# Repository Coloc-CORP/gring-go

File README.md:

# 💍 Smart BLE Ring Project

---

## 🧠 Team

- 🛠️ **Hardware Engineers**: Mathys Pellen, Pierrick Simon
- 👨‍💻 **Software Engineers**: David Cartier, Marius Chritin

---

## 📜 Project Description

Development of an **ultra-compact smart ring** integrating:
- **Bluetooth Low Energy (BLE) communication**
- **Heart rate (BPM) measurement**
- **Activity and movement tracking**
- **Sleep monitoring**
- **Skin temperature measurement**

Mobile application dedicated to:
- Real-time collection of biometric data
- Visualization and analysis of health information
- Synchronization with **Samsung Health** using **Health Connect API**

---

## 🛠️ Project Architecture

### Hardware
- **Microcontroller**: nRF5340 (Nordic Semiconductor)
- **Main Sensors**:
  - MAX86150: Heart Rate and SpO2
  - BHI260AP: 6-axis IMU (motion detection)
  - MAX30205 (or equivalent): Skin temperature sensor
- **Charging**: Wireless charging with Qi standard (STWLC38 IC)
- **PCB**: Flexible PCB (FPC) for compact integration into a ring
- **Casing**: Titanium ring, machined or 3D printed

### Software
- **Embedded firmware**:
  - Developed with **nRF Connect SDK** (Zephyr RTOS)
  - Standard BLE GATT communication
  - OTA DFU (Firmware update over Bluetooth) supported
- **Android Application**:
  - Developed with **Android Studio**
  - BLE Central communication
  - Integration with **Samsung Health** via **Health Connect**

---

## 📂 Project Folder Structure

```plaintext
/README.md           → Main project documentation
/HW/                 → Hardware designs (schematics, PCB layouts, datasheets)
                     → 3D models of the ring (STEP, STL, F3D formats)
/SW/                 → Embedded firmware for nRF5340 (Zephyr)
                     → Android Studio mobile app project
/doc/                → Specifications, technical documents, research notes
```

---

## 🧩 Technologies and Tools

- **nRF Connect SDK** (Zephyr RTOS, Nordic Semiconductor)
- **Segger Embedded Studio** or **VS Code + nRF Connect Extensions**
- **KiCad** for PCB design
- **OnShape / SolidWorks** for 3D modeling
- **Android Studio** for mobile app development
- **GitHub** for project management and version control

---

## 📈 Roadmap

- [x] Requirements and specifications definition
- [x] Component selection
- [ ] BLE basic firmware development
- [ ] BLE mobile application creation
- [ ] First prototype PCB design
- [ ] Hardware prototype fabrication
- [ ] Full system integration and testing
- [ ] Low-power optimization
- [ ] Final miniaturization and industrialization

---

## ⚡ Inspirations

- Samsung Galaxy Ring
- Oura Ring Gen 3

---

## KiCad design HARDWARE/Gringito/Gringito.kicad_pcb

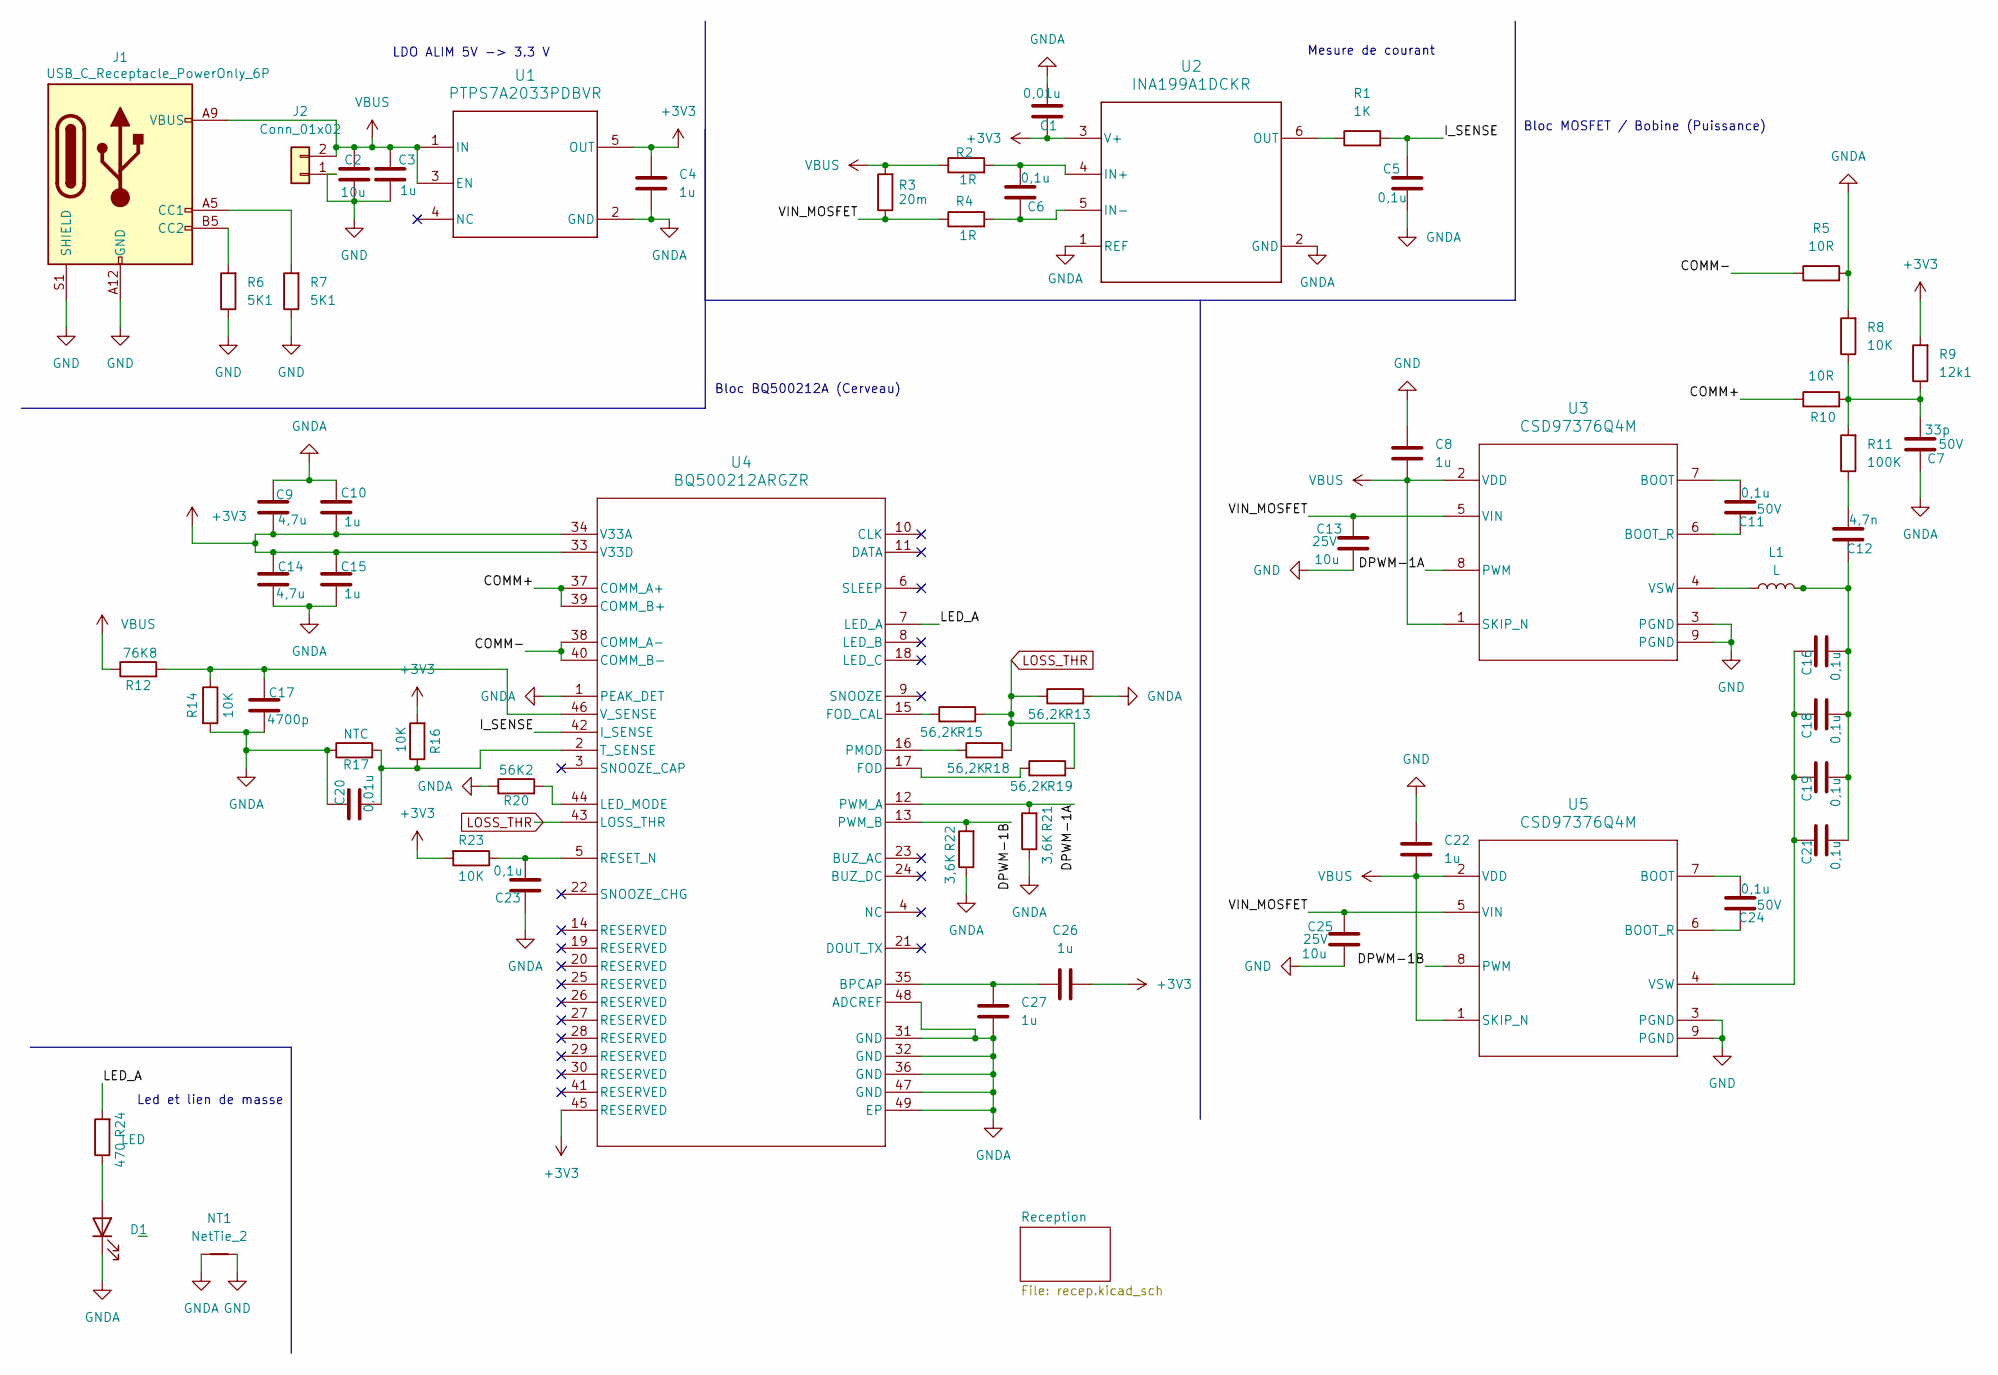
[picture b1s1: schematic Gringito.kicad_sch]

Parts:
C1, C20: 0,01u; C_0805_2012Metric
C2: 10u; C_0805_2012Metric
C3, C4, C8, C10, C15, C22, C26, C27: 1u; C_0805_2012Metric
C5, C6, C23: 0,1u; C_0805_2012Metric
C7: 33p; C_0805_2012Metric; voltage 50V
C9, C14: 4,7u; C_0805_2012Metric
C11, C24: 0,1u; C_0805_2012Metric; voltage 50V
C12: 4,7n; C_0805_2012Metric
C13: 10u; C_0805_2012Metric; Voltage 25V
C16, C18, C19, C21: 0,1u; C_1206_3216Metric_Pad1.33x1.80mm_HandSolder
C17: 4700p; C_0805_2012Metric
C25: 10u; C_0805_2012Metric; voltage 25V
D1: LED; LED_0805_2012Metric
J1: USB_C_Receptacle_PowerOnly_6P; USB_C_Receptacle_GCT_USB4135-GF-A_6P_TopMnt_Horizontal
J2: Conn_01x02; PinHeader_1x02_P2.54mm_Vertical
L1: L; SolderWire-1.5sqmm_1x02_P6mm_D1.7mm_OD3mm
NT1: NetTie_2; NetTie-2_SMD_Pad0.5mm
R1: 1K; R_0805_2012Metric_Pad1.20x1.40mm_HandSolder
R2, R4: 1R; R_0805_2012Metric_Pad1.20x1.40mm_HandSolder
R3: 20m; R_0805_2012Metric_Pad1.20x1.40mm_HandSolder
R5, R10: 10R; R_0805_2012Metric_Pad1.20x1.40mm_HandSolder
R6, R7: 5K1; R_0805_2012Metric_Pad1.20x1.40mm_HandSolder
R8, R14, R16, R23: 10K; R_0805_2012Metric_Pad1.20x1.40mm_HandSolder
R9: 12k1; R_0805_2012Metric_Pad1.20x1.40mm_HandSolder
R11: 100K; R_0805_2012Metric_Pad1.20x1.40mm_HandSolder
R12: 76K8; R_0805_2012Metric_Pad1.20x1.40mm_HandSolder
R13, R15, R18, R19: 56,2K; R_0805_2012Metric_Pad1.20x1.40mm_HandSolder
R17: NTC; R_0805_2012Metric_Pad1.20x1.40mm_HandSolder
R20: 56K2; R_0805_2012Metric_Pad1.20x1.40mm_HandSolder
R21, R22: 3,6K; R_0805_2012Metric_Pad1.20x1.40mm_HandSolder
R24: 470; R_0805_2012Metric_Pad1.20x1.40mm_HandSolder
U1: PTPS7A2033PDBVR; DBV0005A-IPC_A
U2: INA199A1DCKR; DCK0006A_N
U3, U5: CSD97376Q4M; DPC0008A
U4: BQ500212ARGZR; RGZ0048A

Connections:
+3V3: C1.1, C4.1, C9.2, C10.2, C14.1, C15.1, C26.1, R9.2, R16.2, R23.2, U1.5 (OUT), U2.3 (V+), U4.33 (V33D), U4.34 (V33A), U4.45 (RESERVED)
/COMM+: R10.1, U4.37 (COMM_A+), U4.39 (COMM_B+)
/COMM-: R5.1, U4.38 (COMM_A-), U4.40 (COMM_B-)
/DPWM-1A: R21.2, U3.8 (PWM), U4.12 (PWM_A)
/DPWM-1B: R22.2, U4.13 (PWM_B), U5.8 (PWM)
/I_SENSE: C5.1, R1.2, U4.42 (I_SENSE)
/LED_A: R24.2, U4.7 (LED_A)
/VIN_MOSFET: C13.1, C25.1, R3.1, R4.1, U3.5 (VIN), U5.5 (VIN)
GND: C2.2, C3.2, C8.2, C13.2, C22.2, C25.2, J1.A12 (GND), J1.B12 (GND), J1.S1 (SHIELD), J2.1, NT1.2, R6.1, R7.1, U3.3 (PGND), U3.9 (PGND), U3.V, U5.3 (PGND), U5.9 (PGND), U5.V
GNDA: C1.2, C4.2, C5.2, C7.1, C9.1, C10.1, C14.2, C15.2, C17.2, C20.1, C23.1, C27.1, D1.1 (K), NT1.1, R5.2, R8.2, R13.2, R14.2, R17.1, R20.1, R21.1, R22.1, U1.2 (GND), U2.1 (REF), U2.2 (GND), U4.1 (PEAK_DET), U4.31 (GND), U4.32 (GND), U4.36 (GND), U4.47 (GND), U4.48 (ADCREF), U4.49 (EP), U4.V
LOSS_THR: R13.1, R15.2, R18.2, R19.2, U4.43 (LOSS_THR)
unnamed: C7.2, R8.1, R9.1, R10.2, R11.2
unnamed: C12.1, C16.2, C18.2, C19.2, C21.2, L1.2
unnamed: C12.2, R11.1
unnamed: D1.2 (A), R24.1
unnamed: J1.A5 (CC1), R7.2
unnamed: J1.B5 (CC2), R6.2
unnamed: C6.2, R2.2, U2.4 (IN+)
unnamed: C6.1, R4.2, U2.5 (IN-)
unnamed: R1.1, U2.6 (OUT)
unnamed: C11.2, U3.7 (BOOT)
unnamed: C11.1, U3.6 (BOOT_R)
unnamed: L1.1, U3.4 (VSW)
unnamed: C26.2, C27.2, U4.35 (BPCAP)
unnamed: R19.1, U4.17 (FOD)
unnamed: R15.1, U4.15 (FOD_CAL)
unnamed: R20.2, U4.44 (LED_MODE)
unnamed: R18.1, U4.16 (PMOD)
unnamed: C23.2, R23.1, U4.5 (RESET_N)
unnamed: C20.2, R16.1, R17.2, U4.2 (T_SENSE)
unnamed: C17.1, R12.2, R14.1, U4.46 (V_SENSE)
unnamed: C24.2, U5.7 (BOOT)
unnamed: C24.1, U5.6 (BOOT_R)
unnamed: C16.1, C18.1, C19.1, C21.1, U5.4 (VSW)
VBUS: C2.1, C3.1, C8.1, C22.1, J1.A9 (VBUS), J1.B9 (VBUS), J2.2, R2.1, R3.2, R12.1, U1.1 (IN), U1.3 (EN), U3.1 (SKIP_N), U3.2 (VDD), U5.1 (SKIP_N), U5.2 (VDD)

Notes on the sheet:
Bloc BQ500212A (Cerveau)
Led et lien de masse
Bloc MOSFET / Bobine (Puissance)
LDO ALIM 5V -> 3.3 V
Mesure de courant

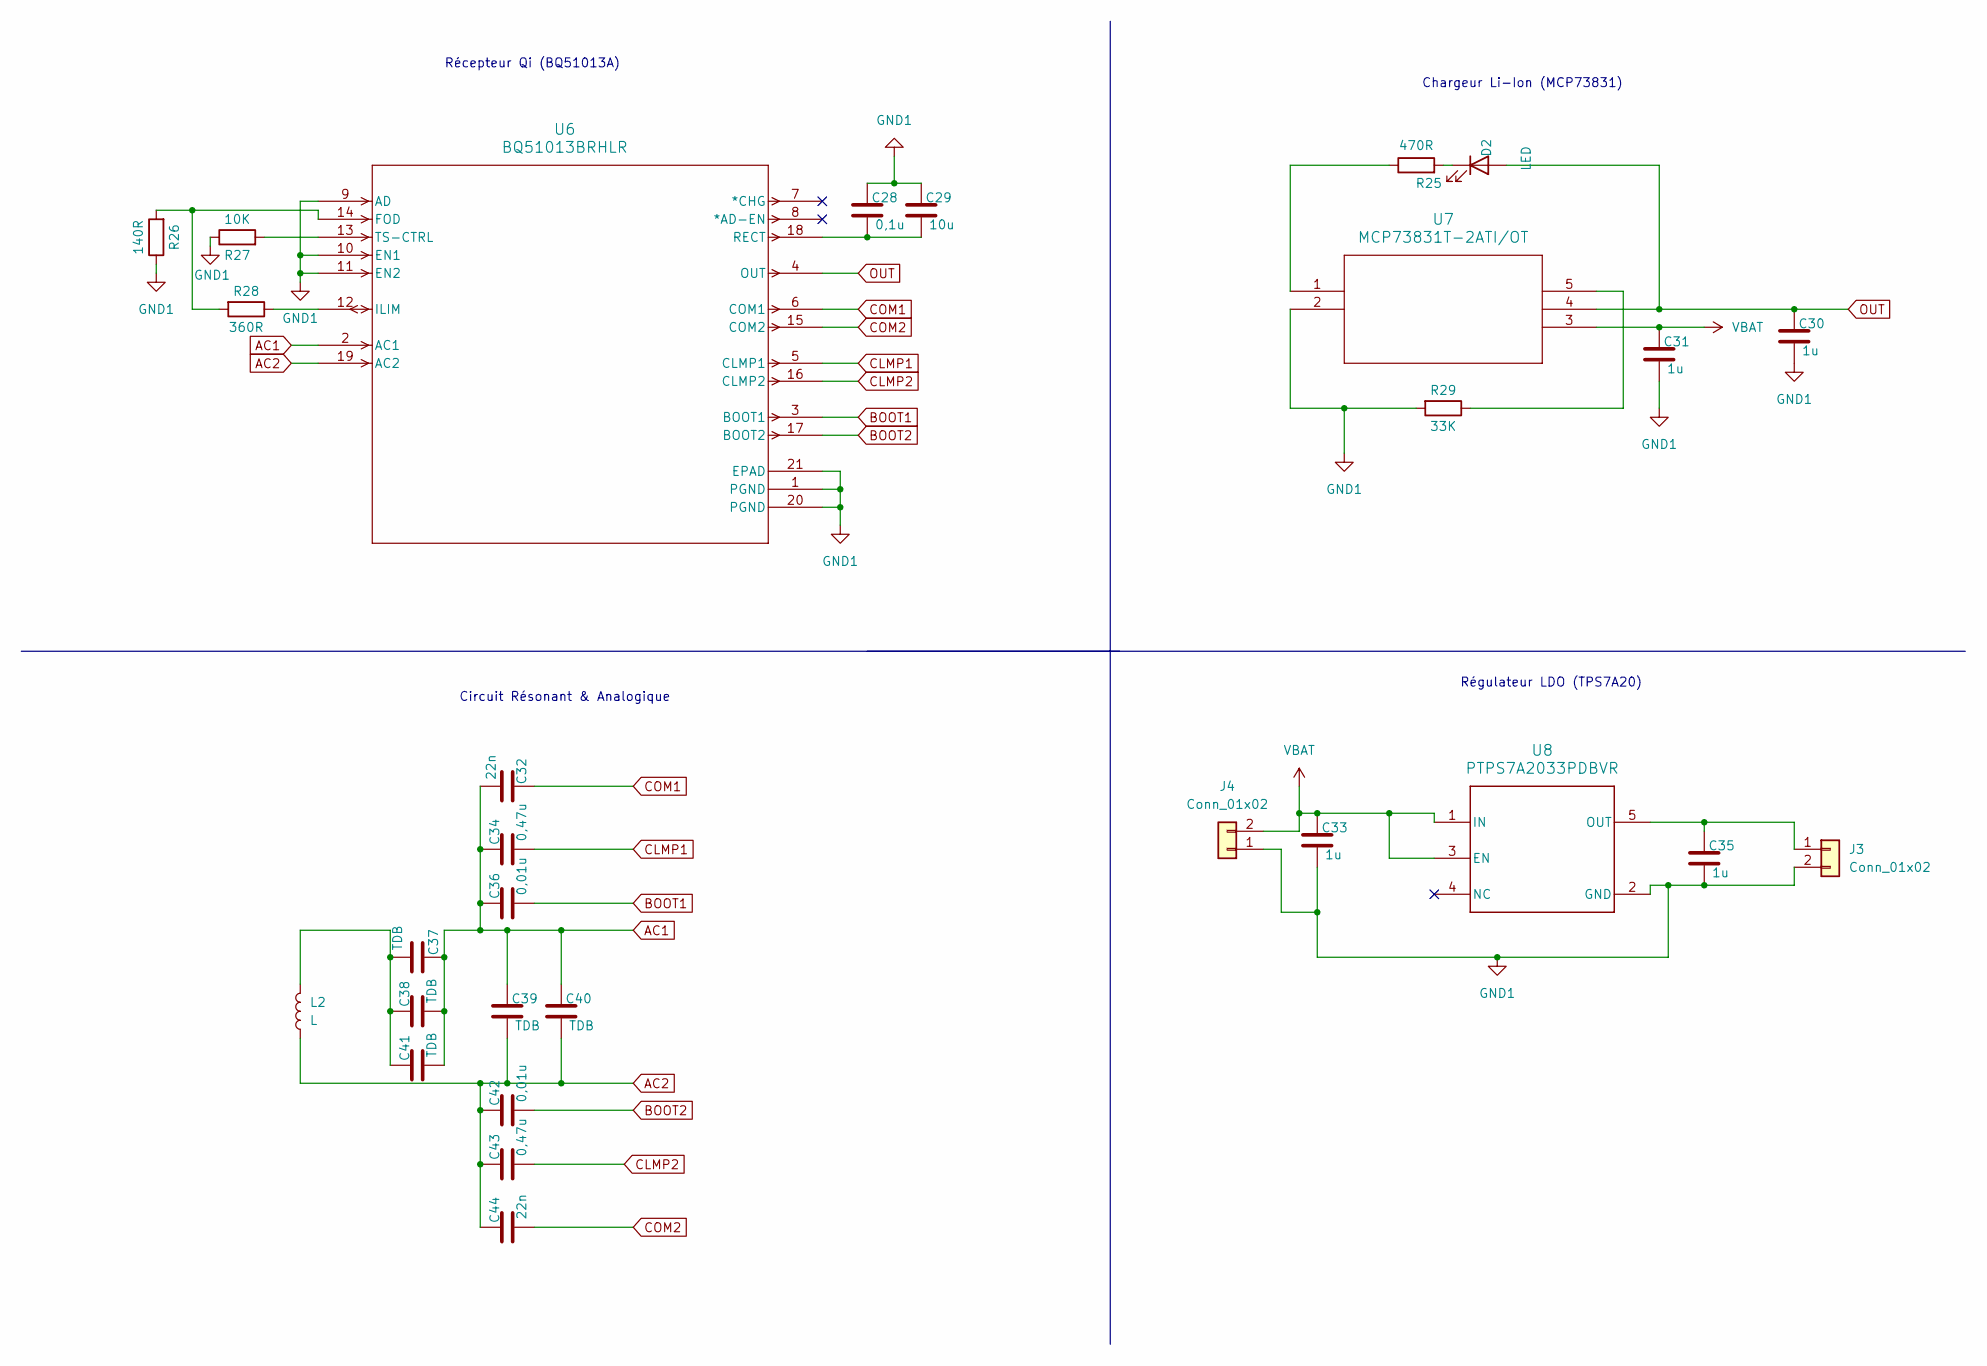
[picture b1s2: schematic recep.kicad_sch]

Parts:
C28: 0,1u; C_0805_2012Metric
C29: 10u; C_0805_2012Metric
C30, C31, C33, C35: 1u; C_0805_2012Metric
C32, C44: 22n; C_0805_2012Metric
C34, C43: 0,47u; C_0805_2012Metric
C36, C42: 0,01u; C_0805_2012Metric
C37, C38, C39, C40, C41: TDB; C_0805_2012Metric
D2: LED; LED_0805_2012Metric
J3, J4: Conn_01x02; PinHeader_1x02_P2.54mm_Vertical
L2: L; SolderWire-1.5sqmm_1x02_P6mm_D1.7mm_OD3mm
R25: 470R; R_0805_2012Metric_Pad1.20x1.40mm_HandSolder
R26: 140R; R_0805_2012Metric_Pad1.20x1.40mm_HandSolder
R27: 10K; R_0805_2012Metric_Pad1.20x1.40mm_HandSolder
R28: 360R; R_0805_2012Metric_Pad1.20x1.40mm_HandSolder
R29: 33K; R_0805_2012Metric_Pad1.20x1.40mm_HandSolder
U6: BQ51013BRHLR; RHL20_2P05X3P05
U7: MCP73831T-2ATI/OT; SOT-23-5_MC_MCH
U8: PTPS7A2033PDBVR; DBV0005A-IPC_A

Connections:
AC1: C32.2, C34.1, C36.1, C37.1, C38.2, C39.1, C40.1, C41.2, U6.2 (AC1)
AC2: C39.2, C40.2, C42.1, C43.1, C44.1, L2.1, U6.19 (AC2)
BOOT1: C36.2, U6.3 (BOOT1)
BOOT2: C42.2, U6.17 (BOOT2)
CLMP1: C34.2, U6.5 (CLMP1)
CLMP2: C43.2, U6.16 (CLMP2)
COM1: C32.1, U6.6 (COM1)
COM2: C44.2, U6.15 (COM2)
GND1: C28.1, C29.1, C30.2, C31.2, C33.2, C35.2, J3.2, J4.1, R26.1, R27.1, R29.2, U6.1 (PGND), U6.9 (AD), U6.10 (EN1), U6.11 (EN2), U6.20 (PGND), U6.21 (EPAD), U6.V, U7.2, U8.2 (GND)
unnamed: C37.2, C38.1, C41.1, L2.2
unnamed: D2.1 (K), R25.2
unnamed: C35.1, J3.1, U8.5 (OUT)
unnamed: R25.1, U7.1
unnamed: R29.1, U7.5
unnamed: R26.2, R28.2, U6.14 (FOD)
unnamed: R28.1, U6.12 (ILIM)
unnamed: C28.2, C29.2, U6.18 (RECT)
unnamed: R27.2, U6.13 (TS-CTRL)
OUT: C30.1, D2.2 (A), U6.4 (OUT), U7.4
VBAT: C31.1, C33.1, J4.2, U7.3, U8.1 (IN), U8.3 (EN)

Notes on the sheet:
Récepteur Qi (BQ51013A)
Chargeur Li-Ion (MCP73831)
Circuit Résonant & Analogique
Régulateur LDO (TPS7A20)

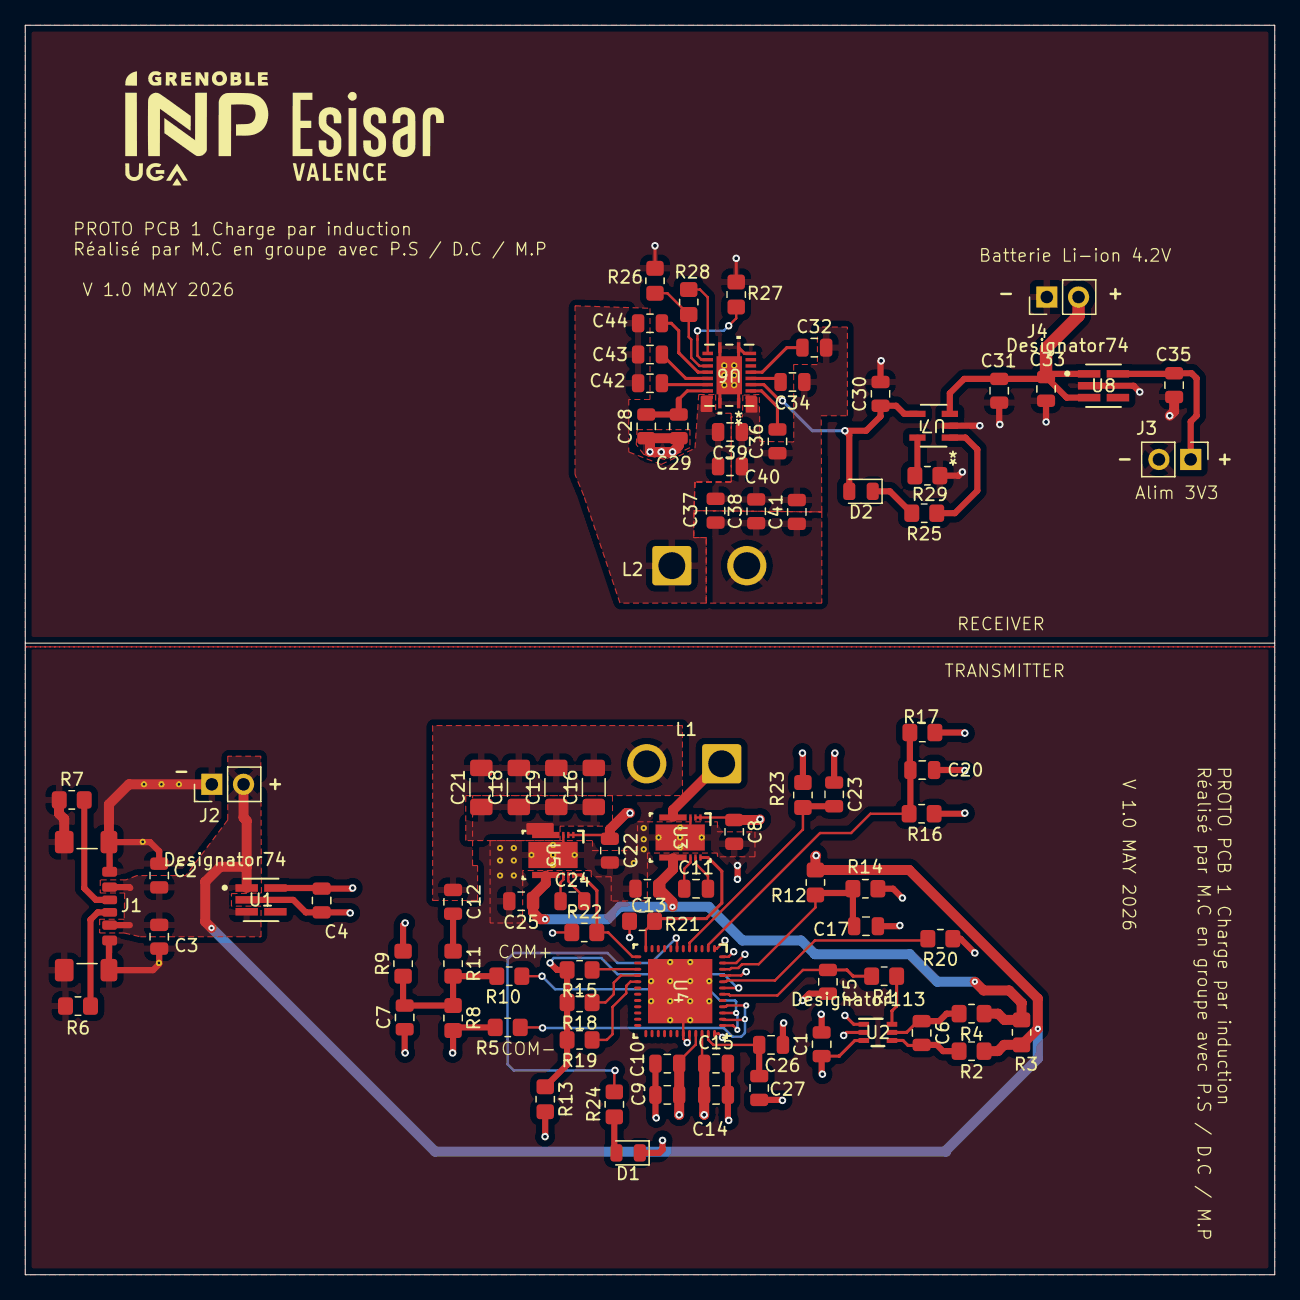
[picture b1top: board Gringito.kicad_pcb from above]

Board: 4 copper layers, 100.0 x 100.0 mm, 90 parts (0 on the bottom side), 55 nets.

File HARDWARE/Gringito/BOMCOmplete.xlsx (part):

Quantité | Références | Type | Valeur / MPN | Boîtier | Spécifications et Filtres (Mouser / Digi-Key) | ref | Ref mouser | Prix |  | Stock ? | A commander | Prix a commander
1.0 | U4 | Puce | BQ500212ARGZR | VQFN-48 | Contrôleur Émetteur Qi |  | https://www.mouser.fr/c/?q=BQ500212ARGZR | 7.62 |  | 6.0 | 0.0 | 0
1.0 | U6 | Puce | BQ51013BRHLR | VQFN-20 | Contrôleur Récepteur Qi |  | https://www.mouser.fr/ProductDetail/Texas-Instruments/BQ5101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 | 3.1 |  | 1.0 | 2.0 | 6.2
2.0 | U3, U5 | Puce | CSD97376Q4M | VSON-8 | Power Stage NexFET |  | https://www.mouser.fr/ProductDetail/Texas-Instruments/CSD973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 | 1.85 |  | 0.0 | 6.0 | 11.1
2.0 | U1, U8 | Puce | PTPS7A2033PDBVR | SOT-23-5 | LDO 3.3V |  | https://www.mouser.fr/ProductDetail/Texas-Instruments/TPS7A2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 | 0.275 |  | 0.0 | 6.0 | 1.65
1.0 | U2 | Puce | INA199A1DCKR | SC-70-6 | Amplificateur de mesure de courant |  | https://www.mouser.fr/ProductDetail/Texas-Instruments/INA199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 | 0.499 |  | 0.0 | 3.0 | 1.497
1.0 | U7 | Puce | MCP73831T-2ATI/OT | SOT-23-5 | Chargeur Li-Ion |  | https://www.mouser.fr/ProductDetail/Microchip-Technology/MCP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 | 0.654 |  | 1.0 | 2.0 | 1.308
1.0 | C7 | Condensateur | 33pF | 805.0 | Diélectrique C0G/NP0, Tension 50V min | VJ0805A330KXAAC | https://www.mouser.fr/ProductDetail/Vishay-Vitramon/VJ0805A3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 | 0.189 |  | 0.0 | 10.0 | 1.89 | Prix total
2.0 | C12, C17 | Condensateur | 4.7nF (4700pF) | 805.0 | Diélectrique C0G/NP0, Tension 50V min | CGA4C2C0G1H472J | https://www.mouser.fr/ProductDetail/TDK/CGA4C2C0G1H472J060AA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 | 0.071 |  | 0.0 | 20.0 | 1.42 | 63.223
4.0 | C1, C20, C36, C42 | Condensateur | 0.01µF (10nF) | 805.0 | Diélectrique C0G/NP0, Tension 50V min | CGA4C2C0G1H103J | https://www.mouser.fr/ProductDetail/TDK/C2012C0G1H103J060AA?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 | 0.103 |  | 0.0 | 20.0 | 2.06
2.0 | C32, C44 | Condensateur | 22nF | 805.0 | Diélectrique C0G/NP0, Tension 50V min | CGA4J2C0G1H223J | https://www.mouser.fr/ProductDetail/TDK/CGA4J2C0G1H223J125AA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 | 0.12 |  | 0.0 | 10.0 | 1.2
2.0 | C34, C43 | Condensateur | 0.47µF (470nF) | 805.0 | Diélectrique X7R, Tension 50V min | C0805C474J5REC7210 | https://www.mouser.fr/ProductDetail/KEMET/C0805C474J5REC7210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 | 0.153 |  | 0.0 | 10.0 | 1.53
5.0 | C37, C38, C39, C40, C41 | Condensateur | TDB | 805.0 | Prévoir des assortiments C0G de quelques nF pour le réglage au labo |  |  |  |  |  |  | 0
5.0 | Pour C37 à C41 | Condensateur | 2.2 nF (2200 pF) | 805.0 | Diélectrique C0G/NP0, Tension 50V min | CGA4J3C0G2E222J | https://www.mouser.fr/ProductDetail/TDK/CGA4J3C0G2E222J125AA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 | 0.093 |  |  | 10.0 | 0.93
5.0 | Pour C37 à C41 | Condensateur | 1 nF (1000 pF) | 805.0 | Diélectrique C0G/NP0, Tension 50V min | AC805JRNPO0BN102 | https://www.mouser.fr/ProductDetail/YAGEO/AC0805JRNPO0BN102?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 | 0.089 |  | 0.0 | 10.0 | 0.89
5.0 | Pour C37 à C41 | Condensateur | 470 pF | 805.0 | Diélectrique C0G/NP0, Tension 50V min | CC0805JPNPO9BN471 | https://www.mouser.fr/ProductDetail/YAGEO/CC0805JPNPO9BN471?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 | 0.037 |  | 0.0 | 10.0 | 0.37
5.0 | Pour C37 à C41 | Condensateur | 220 pF | 805.0 | Diélectrique C0G/NP0, Tension 50V min | CGA4C4C0G2W221J060AA | https://www.mouser.fr/ProductDetail/TDK/CGA4C4C0G2W221J060AA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 | 0.077 |  | 0.0 | 10.0 | 0.77
5.0 | Pour C37 à C41 | Condensateur | 100 pF | 805.0 | Diélectrique C0G/NP0, Tension 50V min |  | AVEC C16 C18 |  |  |  |  | 0
5.0 | Pour C37 à C41 | Condensateur | 47 pF | 805.0 | Diélectrique C0G/NP0, Tension 50V min | C0805C470JDGACTU | https://www.mouser.fr/ProductDetail/KEMET/C0805C470JDGACTU?q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 | 0.19 |  | 0.0 | 10.0 | 1.9
5.0 | Pour C37 à C41 | Condensateur | 22 pF | 805.0 | Diélectrique C0G/NP0, Tension 50V min | VJ0805A220JXCCW1BC | https://www.mouser.fr/ProductDetail/Vishay-Vitramon/VJ0805A2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 | 0.12 |  | 0.0 | 10.0 | 1.2
4.0 | C2, C13, C25, C29 | Condensateur | 10µF | 805.0 | Diélectrique X5R ou X7R, Tension 50V min | GRM21BR61H106KE43L | https://www.mouser.fr/ProductDetail/Murata-Electronics/GRM21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 | 0.109 |  | 0.0 | 20.0 | 2.18
2.0 | C9, C14 | Condensateur | 4.7µF | 805.0 | Diélectrique X5R ou X7R, Tension 25V min | CGA4J1X7R1H475K125AC | https://www.mouser.fr/ProductDetail/TDK/CGA4J1X7R1H475K125AC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 | 0.224 |  | 0.0 | 10.0 | 2.24
12.0 | C3, C4, C8, C10, C15, C22, C26, C27, C30, C31, C33, C35 | Condensateur | 1µF | 805.0 | Diélectrique X7R, Tension 25V min | C2012X7R1H105K | https://www.mouser.fr/ProductDetail/TDK/C2012X7R1H105K125AB?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 | 0.099 |  | 0.0 | 30.0 | 2.97
6.0 | C5, C6, C11, C23, C24, C28 | Condensateur | 0.1µF (100nF) | 805.0 | Diélectrique X7R, Tension 50V min | KAF21KR72A104KL | https://www.mouser.fr/ProductDetail/KYOCERA-AVX/KAF21KR72A10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 | 0.101 |  | 0.0 | 20.0 | 2.02
4.0 | C16, C18, C19, C21 | Condensateur | 0.1µF (100nF) | 1206.0 | Diélectrique C0G/NP0, Tension 50V min | C3216C0G2A104J6C | https://www.mouser.fr/ProductDetail/TDK/C3216C0G2A104J160AC?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 | 0.362 |  | 0.0 | 20.0 | 7.24
1.0 | R3 | Résistance | 20 mΩ | 805.0 | Tolérance 1%, Current Sense, Puissance 0.25W ou 0.5W | 652-CFN0805FXR020ELF | https://www.mouser.fr/ProductDetail/Bourns/CFN0805-FX-R020EL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 | 0.344 |  | 0.0 | 3.0 | 1.032
5.0 | R13, R15, R18, R19, R20 | Résistance | 56.2 kΩ | 805.0 | Tolérance 1% 50 PPM 0.125W | RGC1/10C5622FTP | https://www.mouser.fr/ProductDetail/Kamaya/RGC1-10C5622FTP?q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 | 0.082 |  | 0.0 | 20.0 | 1.64
1.0 | R9 | Résistance | 12.1 kΩ | 805.0 | Tolérance 1% 50 PPM 0.125W | RT0805FRE0712K1L | https://www.mouser.fr/ProductDetail/YAGEO/RT0805FRE0712K1L?q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 | 0.014 |  | 0.0 | 10.0 | 0.14
1.0 | R12 | Résistance | 76.8 kΩ | 805.0 | Tolérance 1% 50 PPM 0.125W | RT0805FRE0776K8L | https://www.mouser.fr/ProductDetail/YAGEO/RT0805FRE0776K8L?q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 | 0.013 |  | 0.0 | 10.0 | 0.13
1.0 | R26 | Résistance | 140 Ω | 805.0 | Tolérance 1% 50 PPM 0.125W | RT0805FRE07140RL | https://www.mouser.fr/ProductDetail/YAGEO/RT0805FRE07140RL?q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 | 0.014 |  | 0.0 | 10.0 | 0.14
1.0 | R28 | Résistance | 360 Ω | 805.0 | Tolérance 1% 50 PPM 0.125W | RT0805FRE07360RL | https://www.mouser.fr/ProductDetail/YAGEO/RT0805FRE07360RL?q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 | 0.014 |  | 0.0 | 10.0 | 0.14
2.0 | R2, R4 | Résistance | 1 Ω | 805.0 | Tolérance 1% 50 PPM 0.125W | RT0805FRE131RL | https://www.mouser.fr/ProductDetail/YAGEO/RT0805FRE131RL?qs=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 | 0.026 |  | 0.0 | 10.0 | 0.26
2.0 | R5, R10 | Résistance | 10 Ω | 805.0 | Tolérance 1% 50 PPM 0.125W | RE0805FRE0710RL | https://www.mouser.fr/ProductDetail/YAGEO/RE0805FRE0710RL?qs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 | 0.015 |  | 0.0 | 10.0 | 0.15
2.0 | R24, R25 | Résistance | 470 Ω | 805.0 | Tolérance 1% 50 PPM 0.125W | RT0805FRE13470RL | https://www.mouser.fr/ProductDetail/YAGEO/RT0805FRE13470RL?q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 | 0.012 |  | 0.0 | 10.0 | 0.12
1.0 | R1 | Résistance | 1 kΩ | 805.0 | Tolérance 1% 50 PPM 0.125W | RT0805FRE101KL | https://www.mouser.fr/ProductDetail/YAGEO/RT0805FRE101KL?qs=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 | 0.014 |  | 0.0 | 10.0 | 0.14
2.0 | R21, R22 | Résistance | 3.6 kΩ | 805.0 | Tolérance 1% 50 PPM 0.125W | RT0805FRE073K6L | https://www.mouser.fr/ProductDetail/YAGEO/RT0805FRE073K6L?qs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 | 0.014 |  | 0.0 | 10.0 | 0.14
2.0 | R6, R7 | Résistance | 5.1 kΩ | 805.0 | Tolérance 1% 50 PPM 0.125W | RT0805FRE075K1L | https://www.mouser.fr/ProductDetail/YAGEO/RT0805FRE075K1L?qs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 | 0.013 |  | 0.0 | 10.0 | 0.13
5.0 | R8, R14, R16, R23, R27 | Résistance | 10 kΩ | 805.0 | Tolérance 1% 50 PPM 0.125W | RE0805FRE1010KL | https://www.mouser.fr/ProductDetail/YAGEO/RE0805FRE1010KL?qs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 | 0.022 |  | 0.0 | 20.0 | 0.44
1.0 | R29 | Résistance | 33 kΩ | 805.0 | Tolérance 1% 50 PPM 0.125W | RT0805DRE0733KL | https://www.mouser.fr/ProductDetail/YAGEO/RT0805DRE0733KL?qs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 | 0.019 |  | 0.0 | 10.0 | 0.19
1.0 | R11 | Résistance | 100 kΩ | 805.0 | Tolérance 1% 50 PPM 0.125W | RT0805DRE07100KL | https://www.mouser.fr/ProductDetail/YAGEO/RT0805DRE07100KL?q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 | 0.019 |  | 0.0 | 10.0 | 0.19
1.0 | R17 | NTC | 10 kΩ à 25°C | 805.0 | Thermistance NTC, Beta (B) proche de 3380K | B57442V5103J62 | https://www.mouser.fr/ProductDetail/TDK/B57442V5103J062?qs=x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 | 0.361 |  | 0.0 | 3.0 | 1.083
2.0 | D1, D2 | Diode | LED | 805.0 | LED CMS | CMD17-21VRC/TR8 | https://www.mouser.fr/ProductDetail/VCC/CMD17-21VRC-TR8?qs=s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 | 0.473 |  | 0.0 | 6.0 | 2.838
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
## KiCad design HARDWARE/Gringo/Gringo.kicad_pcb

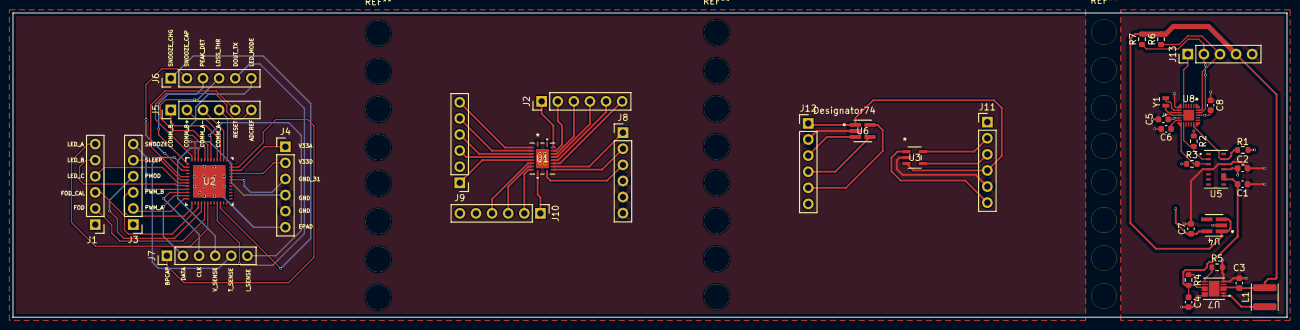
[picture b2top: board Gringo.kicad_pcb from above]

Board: 2 copper layers, 201.0 x 48.0 mm, 38 parts (0 on the bottom side), 70 nets.

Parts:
C1, C3: 10u; C_0603_1608Metric
C2: 100n; C_0603_1608Metric
C4: 22u; C_0603_1608Metric
C5, C6, C7, C8: 1u; C_0603_1608Metric
J1, J2, J3, J5, J6, J7, J8, J9, J10, J11, J12: Conn_01x06; PinHeader_1x06_P2.54mm_Vertical
J4: Alim; PinHeader_1x06_P2.54mm_Vertical
J13: Conn_01x05_Pin; PinHeader_1x05_P2.54mm_Vertical
L1: 2u2; L_APV_ANR4030
R1, R2, R3, R6, R7: 4K7; R_0603_1608Metric
R4: 750K; R_0603_1608Metric
R5: 100K; R_0603_1608Metric
U1: BQ51013ARHLR; RHL20_2P05X3P05
U2: BQ500212ARGZT; RGZ0048A
U3: MCP73831T-2ACI/OT; SOT-23-5_MC_MCH
U4, U6: PTPS7A2018PDBVR; DBV0005A-IPC_A
U5: MAX30101EFD+; 21-1048_F143A5&plus_1_MXM
U7: PAM2401YPADJ; SON12_U-DFN3030-12_DIO-M
U8: MAX32664GTGA+T; 21-100264_T2433&plus_2C_MXM
Y1: 32k768; XTAL_ECX-12_2X1P2_ECS

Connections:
+1V8: C2.1, C5.1, C7.1, C8.1, R1.1, R2.1, R3.1, U4.5 (OUT), U5.11 (VDD), U8.11 (VDD), U8.22 (VDD)
+3.3V: C3.1, J13.4, L1.1, R6.2, R7.2, U4.1 (IN), U4.3 (EN), U7.3 (EN), U7.4 (VIN)
+5V: C1.1, C4.1, R4.2, U5.9 (VLED+), U5.10 (VLED+), U7.9 (OUT), U7.10 (OUT)
GND: C1.2, C2.2, C3.2, C4.2, C5.2, C6.2, C7.2, C8.2, J4.4, J4.5, J8.4, J8.5, J8.6, J11.5, J12.2, J13.5, R5.2, U1.1 (PGND), U1.20 (PGND), U1.21 (EPAD), U2.32 (GND), U2.36 (GND), U2.47 (GND), U3.2 (VSS), U4.2 (GND), U5.4 (PGND), U5.12 (GND), U6.2 (GND), U7.6 (AGND), U7.11 (PGND), U7.12 (PGND), U8.7 (VSS), U8.10 (VSS), U8.25 (EPAD)
HOST_SCL: J13.2, R7.1, U8.23 (SLAVE_SDA)
HOST_SDA: J13.3, R6.1, U8.24 (SLAVE_SCL)
HR_INT: R1.2, U5.13 (*INT), U8.18 (HR_INT)
unnamed: J1.2, U2.17 (FOD)
unnamed: J1.3, U2.15 (FOD_CAL)
unnamed: J1.4, U2.7 (LED_A)
unnamed: J1.5, U2.8 (LED_B)
unnamed: J1.6, U2.18 (LED_C)
unnamed: J2.1, J9.6, U1.2 (AC1), U1.19 (AC2)
unnamed: J2.2, U1.18 (RECT)
unnamed: J2.3, U1.17 (BOOT2)
unnamed: J2.4, U1.16 (CLMP2)
unnamed: J2.5, U1.15 (COM2)
unnamed: J2.6, U1.14 (FOD)
unnamed: J3.2, U2.12 (PWM_A)
unnamed: J3.3, U2.13 (PWM_B)
unnamed: J3.4, J3.5, U2.6 (SLEEP), U2.16 (PMOD)
unnamed: J3.6, U2.9 (SNOOZE)
unnamed: J4.3, U2.31 (GND_31)
unnamed: J4.6, U2.49 (EPAD)
unnamed: J5.1, U2.40 (COMM_B-)
unnamed: J5.2, U2.39 (COMM_B+)
unnamed: J5.3, U2.38 (COMM_A–)
unnamed: J5.4, U2.37 (COMM_A+)
unnamed: J5.5, U2.5 (~RESET)
unnamed: J5.6, U2.48 (ADCREF)
unnamed: J6.1, U2.22 (SNOOZE_CHG)
unnamed: J6.2, U2.3 (SNOOZE_CAP)
unnamed: J6.3, U2.1 (PEAK_DET)
unnamed: J6.4, U2.43 (LOSS_THR)
unnamed: J6.5, U2.21 (DOUT_TX)
unnamed: J6.6, U2.44 (LED_MODE)
unnamed: J7.1, U2.35 (BPCAP)
unnamed: J7.2, U2.11 (DATA)
unnamed: J7.3, U2.10 (CLK)
unnamed: J7.4, U2.46 (V_SENSE)
unnamed: J7.5, U2.2 (T_SENSE)
unnamed: J7.6, U2.42 (I_SENSE)
unnamed: J8.1, U1.13 (TS-CTRL)
unnamed: J8.2, U1.12 (ILIM)
unnamed: J8.3, U1.11 (EN2)
unnamed: J9.1, U1.6 (COM1)
unnamed: J9.3, U1.5 (CLMP1)
unnamed: J9.4, U1.4 (OUT)
unnamed: J9.5, U1.3 (BOOT1)
unnamed: J10.1, U1.10 (EN1/TERM)
unnamed: J10.2, U1.9 (AD)
unnamed: J10.3, U1.8 (*AD-EN)
unnamed: J10.4, U1.7 (*CHG)
unnamed: J11.2, U3.5 (PROG)
unnamed: J11.3, U3.4 (VDD)
unnamed: J11.4, J12.1, U3.3 (VBAT), U6.1 (IN)
unnamed: J11.6, U3.1 (STAT)
unnamed: J12.3, U6.3 (EN)
unnamed: J12.4, U6.4 (NC)
unnamed: J12.5, U6.5 (OUT)
unnamed: L1.2, U7.1 (LX), U7.2 (LX)
unnamed: R4.1, R5.1, U7.7 (FB)
unnamed: U8.9 (32KIN), Y1.1
unnamed: U8.8 (32KOUT), Y1.2
unnamed: C6.1, U8.12 (VCORE)
RST: J13.1, U8.6 (RSTN)
SSR_SCL: R2.2, U5.2 (SCL), U8.14 (SENSOR_SCL)
SSR_SDA: R3.2, U5.3 (SDA), U8.13 (SENSOR_SDA)
V33A: J4.1, U2.34 (V33A)
V33D: J4.2, U2.33 (V33D)

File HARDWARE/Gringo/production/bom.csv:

Designator,Footprint,Quantity,Value,LCSC Part #
"_21, _20, _19, _18, _17, _16, _15, _14, _13, _12, _11, _10, _9, _8, _7, _6, _5, _4, _3, _2, ",,21,,
"C1, C3",0603,2,10u,
C2,0603,1,100n,
C4,0603,1,22u,
"C5, C6, C7, C8",0603,4,1u,
"J1, J10, J11, J12, J2, J3, J5, J6, J7, J8, J9",PinHeader_1x06_P2.54mm_Vertical,11,Conn_01x06,
J13,PinHeader_1x05_P2.54mm_Vertical,1,Conn_01x05_Pin,
J4,PinHeader_1x06_P2.54mm_Vertical,1,Alim,
L1,L_APV_ANR4030,1,2u2,
"R1, R2, R3, R6, R7",0603,5,4K7,
R4,0603,1,750K,
R5,0603,1,100K,
U1,RHL20_2P05X3P05,1,BQ51013ARHLR,
U2,RGZ0048A,1,BQ500212ARGZT,
U3,SOT-23-5_MC_MCH,1,MCP73831T-2ACI/OT,
"U4, U6",DBV0005A-IPC_A,2,PTPS7A2018PDBVR,
U5,21-1048_F143A5&plus_1_MXM,1,MAX30101EFD+,
U7,SON12_U-DFN3030-12_DIO-M,1,PAM2401YPADJ,
U8,21-100264_T2433&plus_2C_MXM,1,MAX32664GTGA+T,
Y1,Crystal_SMD_2012-2Pin_2.0x1.2mm,1,32k768,

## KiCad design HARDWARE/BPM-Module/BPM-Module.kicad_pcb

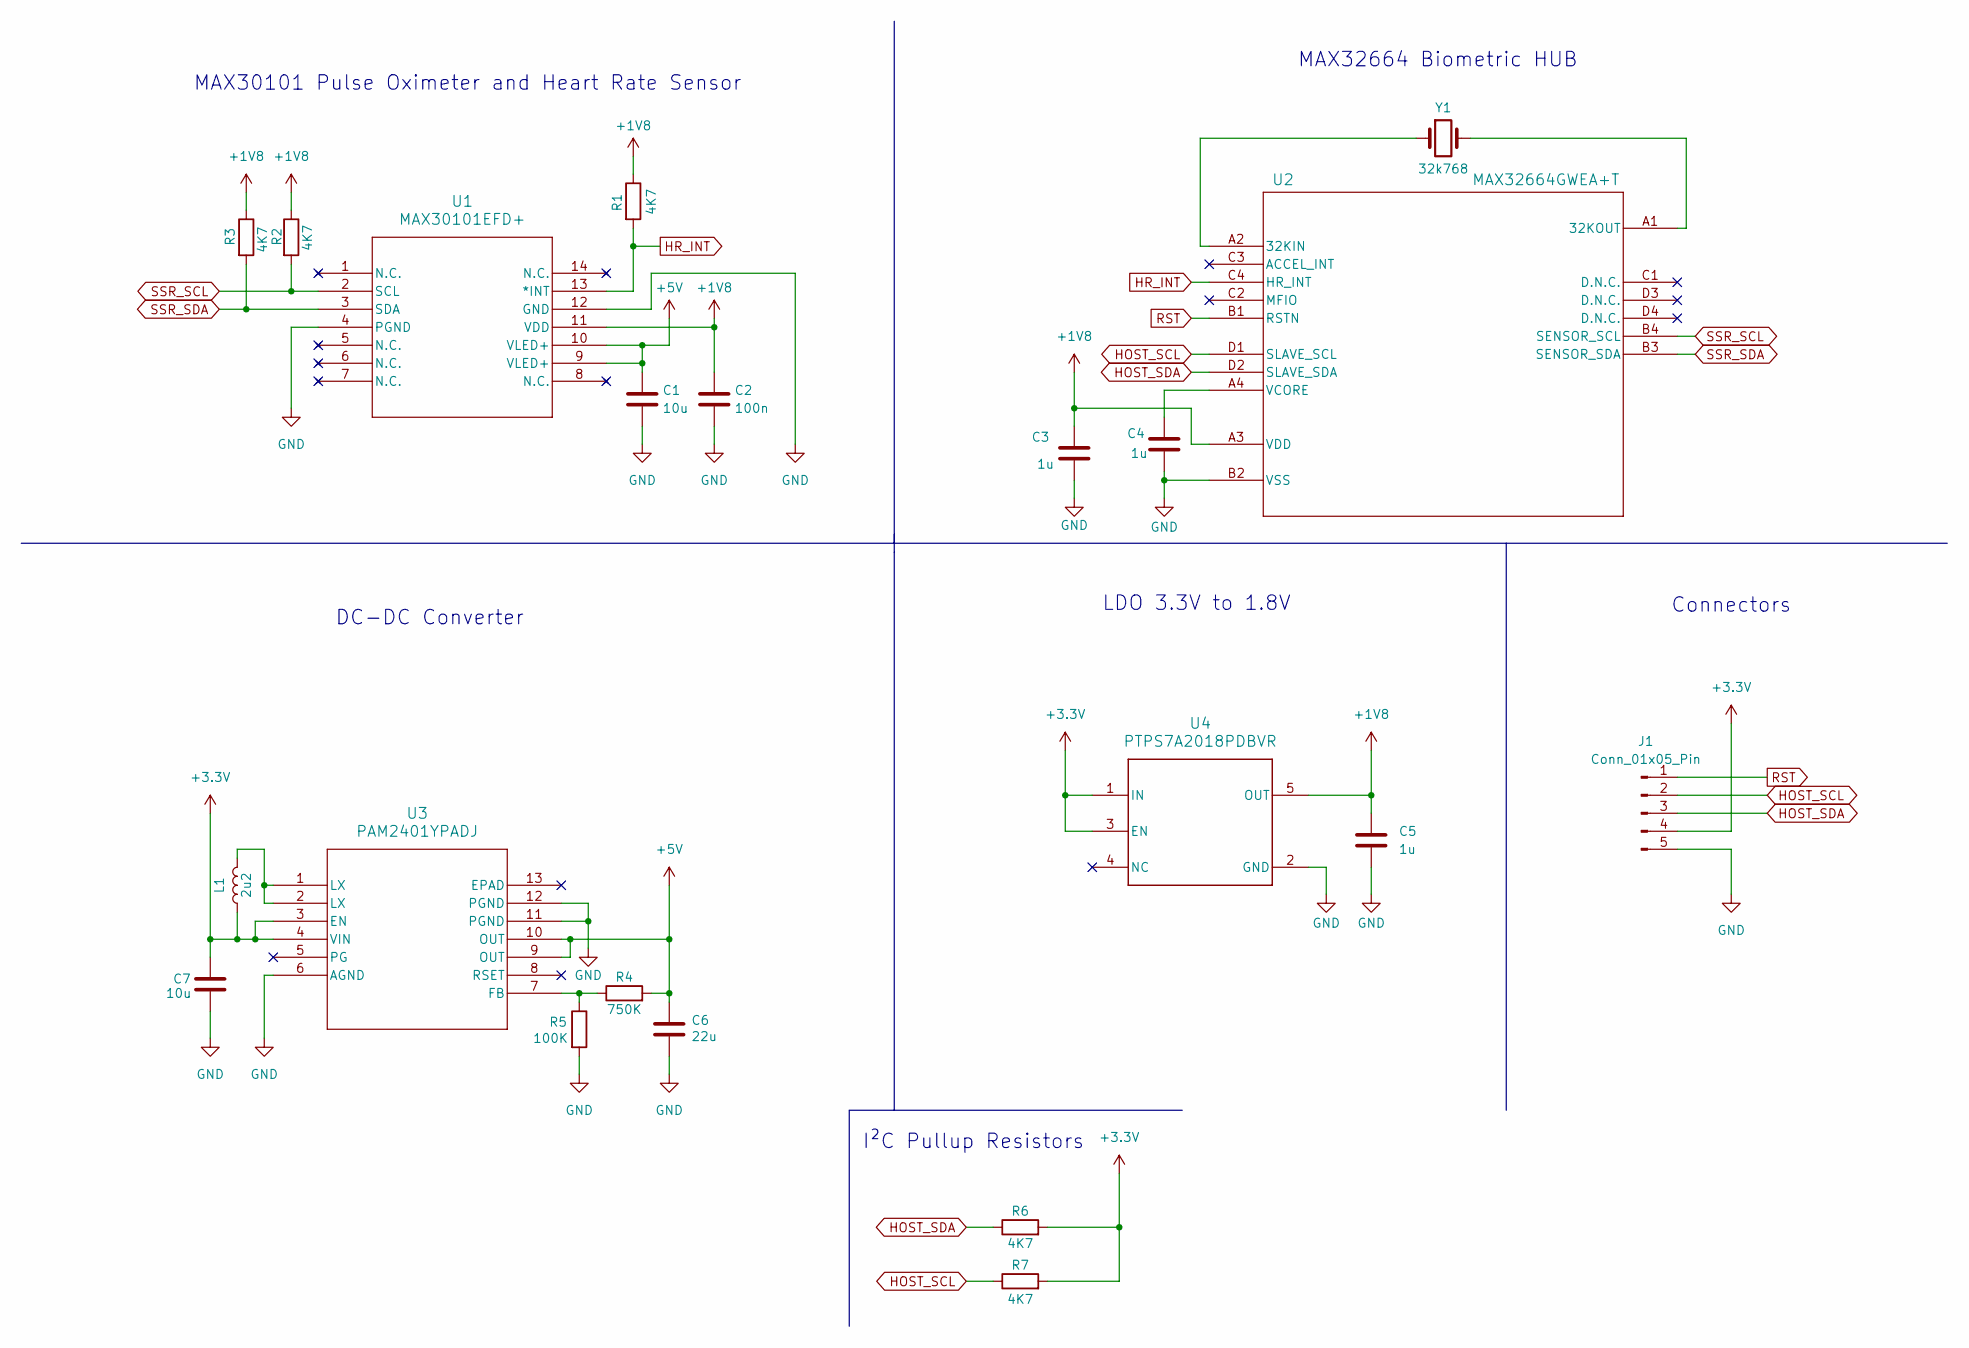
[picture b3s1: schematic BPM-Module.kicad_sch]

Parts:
C1, C7: 10u; C_0603_1608Metric
C2: 100n; C_0603_1608Metric
C3, C4, C5: 1u; C_0603_1608Metric
C6: 22u; C_0603_1608Metric
J1: Conn_01x05_Pin; PinHeader_1x05_P2.54mm_Vertical
L1: 2u2; L_0603_1608Metric
R1, R2, R3, R6, R7: 4K7; R_0603_1608Metric
R4: 750K; R_0603_1608Metric
R5: 100K; R_0603_1608Metric
U1: MAX30101EFD+; 21-1048_F143A5&plus_1_MXM-M
U2: MAX32664GWEA+T; 21-100241A_W161K1&plus_1_MXM
U3: PAM2401YPADJ; SON12_U-DFN3030-12_DIO-M
U4: PTPS7A2018PDBVR; DBV0005A-IPC_A
Y1: 32k768; Crystal_SMD_2012-2Pin_2.0x1.2mm

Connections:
+1V8: C2.1, C3.1, C5.1, R1.1, R2.1, R3.1, U1.11 (VDD), U2.A3 (VDD), U4.5 (OUT)
+3.3V: C7.1, J1.4, L1.1, R6.2, R7.2, U3.3 (EN), U3.4 (VIN), U4.1 (IN), U4.3 (EN)
+5V: C1.1, C6.1, R4.2, U1.9 (VLED+), U1.10 (VLED+), U3.9 (OUT), U3.10 (OUT)
GND: C1.2, C2.2, C3.2, C4.2, C5.2, C6.2, C7.2, J1.5, R5.2, U1.4 (PGND), U1.12 (GND), U2.B2 (VSS), U3.6 (AGND), U3.11 (PGND), U3.12 (PGND), U4.2 (GND)
HOST_SCL: J1.2, R7.1, U2.D1 (SLAVE_SCL)
HOST_SDA: J1.3, R6.1, U2.D2 (SLAVE_SDA)
HR_INT: R1.2, U1.13 (*INT), U2.C4 (HR_INT)
unnamed: L1.2, U3.1 (LX), U3.2 (LX)
unnamed: U2.A2 (32KIN), Y1.1
unnamed: U2.A1 (32KOUT), Y1.2
unnamed: C4.1, U2.A4 (VCORE)
unnamed: R4.1, R5.1, U3.7 (FB)
RST: J1.1, U2.B1 (RSTN)
SSR_SCL: R2.2, U1.2 (SCL), U2.B4 (SENSOR_SCL)
SSR_SDA: R3.2, U1.3 (SDA), U2.B3 (SENSOR_SDA)

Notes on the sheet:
I²C Pullup Resistors
MAX32664 Biometric HUB
LDO 3.3V to 1.8V
Connectors
DC-DC Converter
MAX30101 Pulse Oximeter and Heart Rate Sensor
